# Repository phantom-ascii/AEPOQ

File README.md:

# AEPOQ
## born to be different

AEPOQ was created by a 14 year old kid. I created AEPOQ to study on keyboard layouts and matricies. "Why" you may ask... Well i want to creat a laptop in the next 2 years and what better way to learn about hardware and laptops than making a keyboard (there are proably alot of better ways.) Unfortunately i could not add my full master step die to githubs large file limit and i didnt have time to set up lfs or smth like that cause im leaving for school in 2 hours. Anyways the keyboard is a 68 key 65% keyboard designed for productivity. It has a rotaty switch and an oled to make it special. AND A CANDY HOLDER ON THE RIGHT.Heres some eye candy:

 I used a normal mattix for yhe key switches and a raspberry pi pico for the mcu. the firmware is a test and im not expecting it to work. i will fix it once i actually build the keyboard as that is what i usually do. The keyboard case is at a 6.3~ slant for imprived erganomics. Everything was designed me using models as a guide from open source repositorys. This project is also published on the hackclub programn, forge. I will be using cherry mx keyswitches and generic key caps. The rotary endoer is a ec11 from alps. the oled is a generic 0.91 oled 4 pin header and the mcu is a raspberry pi pico. The keyswitch layout is a generic 65% stagered QWERTY for productivity and general erganomics. If you want to rip any models from this repo go ahead. Its open source anyways.

 Here is the BOM:
 # 65% Custom Keyboard - Master Bill of Materials

## 1. Electronics & Hardware (AliExpress)

| Component | Store | Spec / Description | Price (USD) | Order Link |
| :--- | :--- | :--- | :--- | :--- |
| **Microcontroller** | WeAct Studio Official Store | RP2040 (8MB Black Edition) | $5.16 | [RP2040 Pico Board](https://www.aliexpress.com/item/1005003708090298.html) |
| **Diodes** | Chinese Super Electronic market | 1N4148 SOD-123 SMD Diodes (1000-pack) | $4.54 | [1N4148 SOD-123 Diodes](https://www.aliexpress.com/item/32354597825.html) |
| **Rotary Encoder** | DQLZV Official Store | EC11 Encoder 20mm Half-Handle (5-pack) | $2.85 | [EC11 Rotary Encoder](https://www.aliexpress.com/w/wholesale-digital-encoder-ec11.html) |
| **OLED Display** | diymore Alice1101983 Store | 0.91" 128x32 I2C Display Module | $3.09 | [0.91" I2C OLED Module](https://www.aliexpress.com/item/32815893431.html) |
| **Switches** | The Powerpuff Girls Switch Store | Cherry Switches (70-pack) | $26.58 | [Cherry MX Switches](https://www.aliexpress.com/item/100504669940336.html) |
| **Stabilizers** | YMDK Store | Screw-In PCB Mount Stabilizer Set | $18.62 | [YMDK PCB Stabilizers](https://www.aliexpress.com/item/1005012115758953.html) |
| **Keycaps** | Melokey Store | Line Gradient Side-Shine Cherry PBT | $18.32 | [Side-Shine PBT Keycaps](https://www.aliexpress.com/w/wholesale-keycaps-65.html) |
| **Heat-Set Inserts** | Zenhosit Store | Brass Threaded Inserts M2/M2.5/M3 (220-pack) | $4.91 | [M2 Brass Inserts](https://www.aliexpress.com/item/1005010241559236.html) |
| **Choice Discount** | Choice Discounts | Applied Checkout Savings | -$7.07 | — |
| **AliExpress Shipping** | Choice / Standard | Expedited Combined Delivery | $0.00 | Free |
| **AliExpress Subtotal** | | | **$84.06** | |

---

## 2. PCB Fabrication & 3D Printing (JLCPCB / JLC3DP)

| Item | Service | Description | Price (USD) |
| :--- | :--- | :--- | :--- |
| **PCB Prototypes (`Aepoq_Y7`)** | JLCPCB | White Solder Mask, 1.6 mm, HASL (5-pack) | $22.60 |
| **Keyboard Case (`Case.step`)** | JLC3DP | 9600 Resin, White SLA 3D Print (1 pc) | $88.74 |
| **Keyboard Lid (`Lid.step`)** | JLC3DP | 9600 Resin, White SLA 3D Print (1 pc) | $13.04 |
| **JLCPCB Shipping** | Standard / Express | Package Weight: 3.01 kg | $90.06 |
| **JLCPCB Coupons** | Checkout Coupon | Applied Savings | -$25.00 |
| **JLCPCB Subtotal** | | | **$189.44** |

---

## 3. Total Project Cost

| Category | Amount (USD) |
| :--- | :--- |
| **AliExpress Subtotal** | $84.06 |
| **JLCPCB Subtotal** | $189.44 |
| **Grand Total** | **$273.50** |

the whole build comes out to around $273, with jlcpcb taking up $189 of that. the shipping and case prices ended up pretty high because i intentionally went with a filled interior instead of hollowing it out. i've always hated light, cheap-feeling keyboards, so i wanted this build to have some serious weight to it and feel super solid on the desk even if it meant paying extra for the resin.

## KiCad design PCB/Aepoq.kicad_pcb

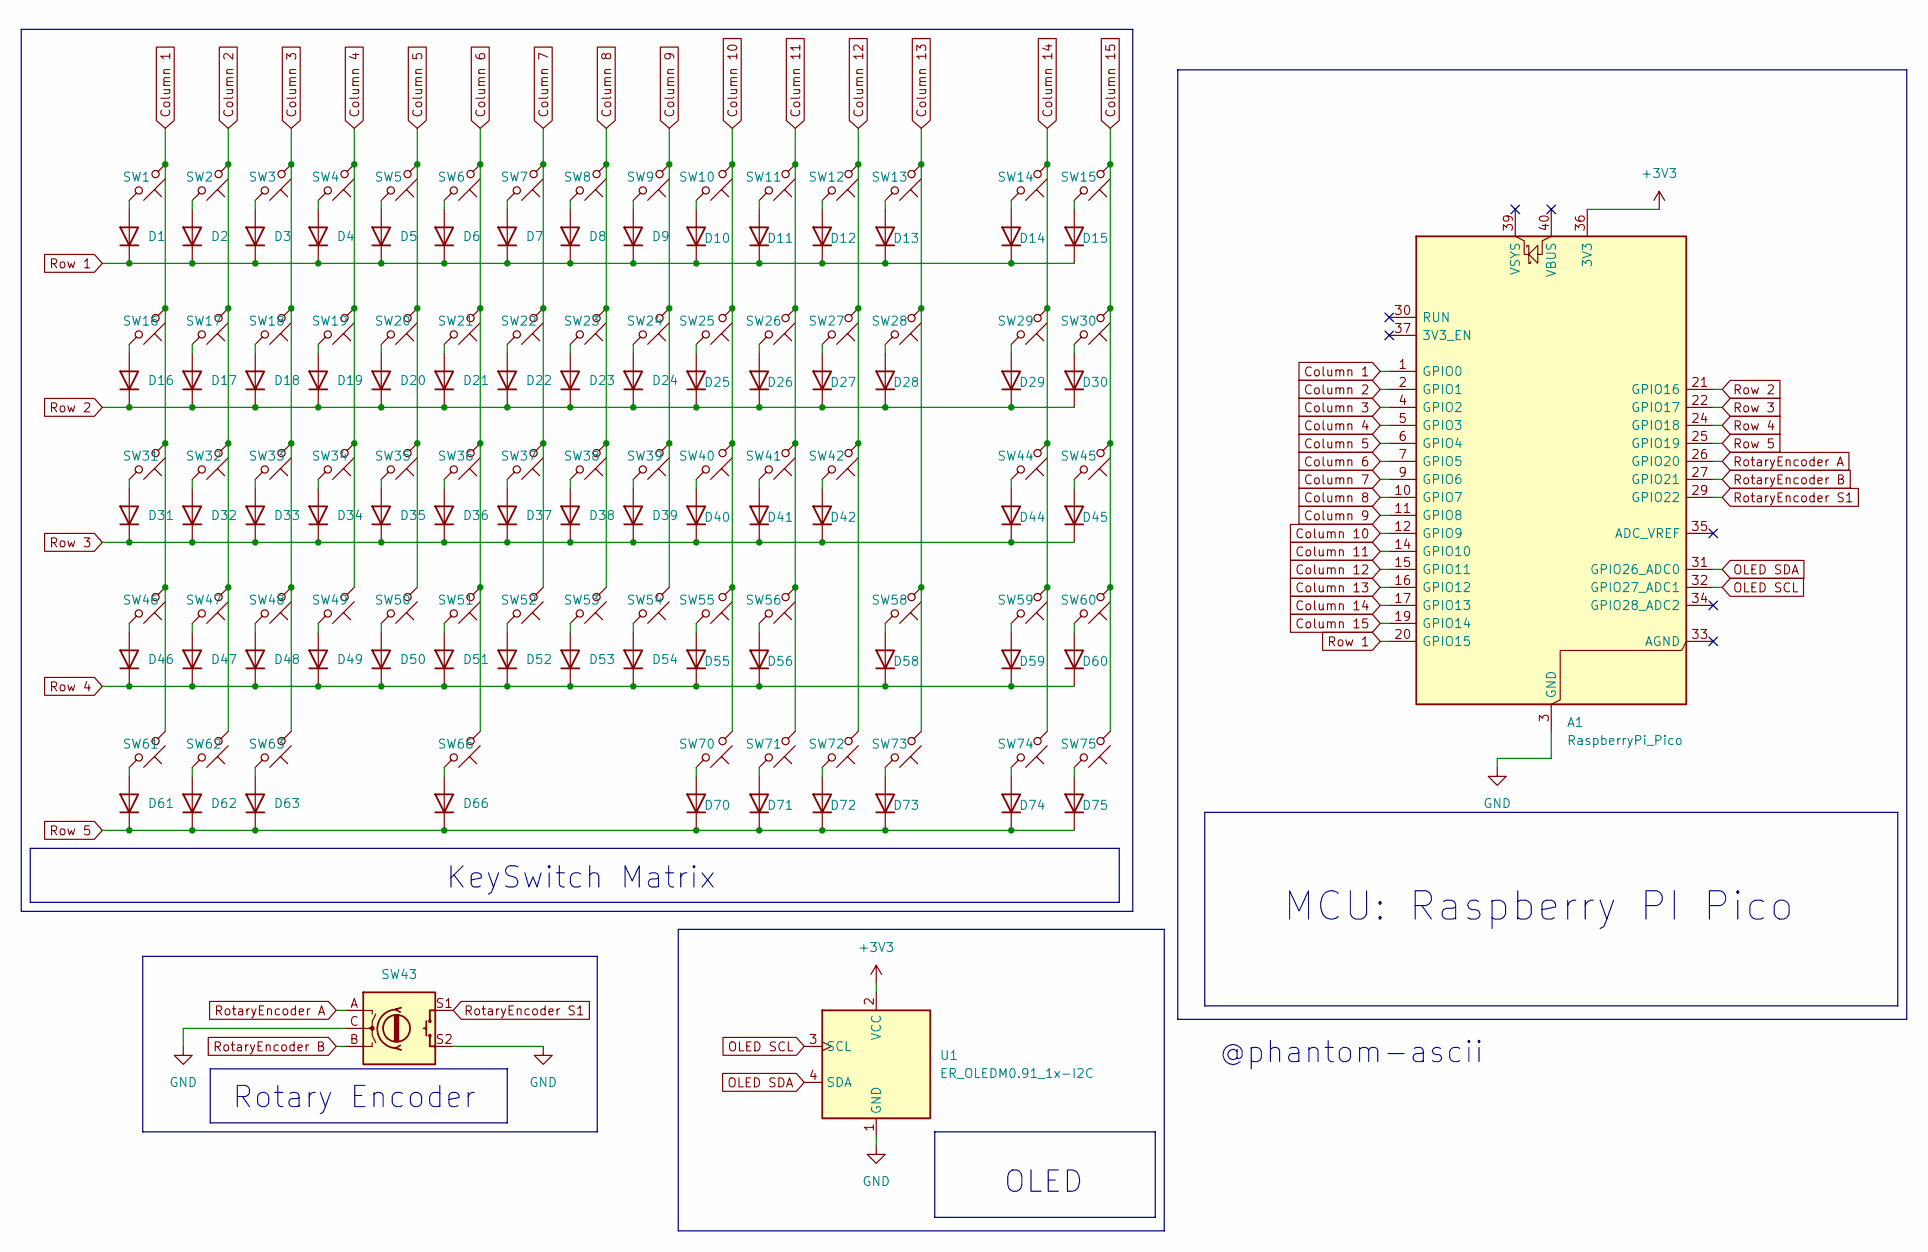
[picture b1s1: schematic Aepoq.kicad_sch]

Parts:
A1: RaspberryPi_Pico; Raspberry_Pi_Pico
D1, D2, D3, D4, D5, D6, D7, D8, D9, D10, D11, D12, D13, D14, D15, D16, D17, D18, D19, D20, D21, D22, D23, D24, D25, D26, D27, D28, D29, D30, D31, D32, D33, D34, D35, D36, D37, D38, D39, D40, D41, D42, D44, D45, D46, D47, D48, D49, D50, D51, D52, D53, D54, D55, D56, D58, D59, D60, D61, D62, D63, D66, D70, D71, D72, D73, D74, D75: 1N4148; D_DO-35_SOD27_P7.62mm_Horizontal
SW1, SW2, SW3, SW4, SW5, SW6, SW7, SW8, SW9, SW10, SW11, SW12, SW13, SW14, SW15, SW16, SW17, SW18, SW19, SW20, SW21, SW22, SW23, SW24, SW25, SW26, SW27, SW28, SW29, SW30, SW31, SW32, SW33, SW34, SW35, SW36, SW37, SW38, SW39, SW40, SW41, SW42, SW44, SW45, SW46, SW47, SW48, SW49, SW50, SW51, SW52, SW53, SW54, SW55, SW56, SW58, SW59, SW60, SW61, SW62, SW63, SW66, SW70, SW71, SW72, SW73, SW74, SW75: MX_SW_solder; SW_MX_1u
SW43: RotaryEncoder_Switch; RotaryEncoder_Alps_EC11E-Switch_Vertical_H20mm
U1: ER_OLEDM0.91_1x-I2C

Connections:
+3V3: A1.36 (3V3), U1.2 (VCC)
Column 1: A1.1 (GPIO0), SW1.1, SW16.1, SW31.1, SW46.1, SW61.1
Column 2: A1.2 (GPIO1), SW2.1, SW17.1, SW32.1, SW47.1, SW62.1
Column 3: A1.4 (GPIO2), SW3.1, SW18.1, SW33.1, SW48.1, SW63.1
Column 4: A1.5 (GPIO3), SW4.1, SW19.1, SW34.1, SW49.1
Column 5: A1.6 (GPIO4), SW5.1, SW20.1, SW35.1, SW50.1
Column 6: A1.7 (GPIO5), SW6.1, SW21.1, SW36.1, SW51.1, SW66.1
Column 7: A1.9 (GPIO6), SW7.1, SW22.1, SW37.1, SW52.1
Column 8: A1.10 (GPIO7), SW8.1, SW23.1, SW38.1, SW53.1
Column 9: A1.11 (GPIO8), SW9.1, SW24.1, SW39.1, SW54.1
Column 10: A1.12 (GPIO9), SW10.1, SW25.1, SW40.1, SW55.1, SW70.1
Column 11: A1.14 (GPIO10), SW11.1, SW26.1, SW41.1, SW56.1, SW71.1
Column 12: A1.15 (GPIO11), SW12.1, SW27.1, SW42.1, SW72.1
Column 13: A1.16 (GPIO12), SW13.1, SW28.1, SW58.1, SW73.1
Column 14: A1.17 (GPIO13), SW14.1, SW29.1, SW44.1, SW59.1, SW74.1
Column 15: A1.19 (GPIO14), SW15.1, SW30.1, SW45.1, SW60.1, SW75.1
GND: A1.3 (GND), A1.8 (GND), A1.13 (GND), A1.18 (GND), A1.23 (GND), A1.28 (GND), A1.38 (GND), SW43.C, SW43.S2, U1.1 (GND)
unnamed: D1.2 (A), SW1.2
unnamed: D2.2 (A), SW2.2
unnamed: D3.2 (A), SW3.2
unnamed: D4.2 (A), SW4.2
unnamed: D5.2 (A), SW5.2
unnamed: D6.2 (A), SW6.2
unnamed: D7.2 (A), SW7.2
unnamed: D8.2 (A), SW8.2
unnamed: D9.2 (A), SW9.2
unnamed: D10.2 (A), SW10.2
unnamed: D11.2 (A), SW11.2
unnamed: D12.2 (A), SW12.2
unnamed: D13.2 (A), SW13.2
unnamed: D14.2 (A), SW14.2
unnamed: D15.2 (A), SW15.2
unnamed: D16.2 (A), SW16.2
unnamed: D17.2 (A), SW17.2
unnamed: D18.2 (A), SW18.2
unnamed: D19.2 (A), SW19.2
unnamed: D20.2 (A), SW20.2
unnamed: D21.2 (A), SW21.2
unnamed: D22.2 (A), SW22.2
unnamed: D23.2 (A), SW23.2
unnamed: D24.2 (A), SW24.2
unnamed: D25.2 (A), SW25.2
unnamed: D26.2 (A), SW26.2
unnamed: D27.2 (A), SW27.2
unnamed: D28.2 (A), SW28.2
unnamed: D29.2 (A), SW29.2
unnamed: D30.2 (A), SW30.2
unnamed: D31.2 (A), SW31.2
unnamed: D32.2 (A), SW32.2
unnamed: D33.2 (A), SW33.2
unnamed: D34.2 (A), SW34.2
unnamed: D35.2 (A), SW35.2
unnamed: D36.2 (A), SW36.2
unnamed: D37.2 (A), SW37.2
unnamed: D38.2 (A), SW38.2
unnamed: D39.2 (A), SW39.2
unnamed: D40.2 (A), SW40.2
unnamed: D41.2 (A), SW41.2
unnamed: D42.2 (A), SW42.2
unnamed: D44.2 (A), SW44.2
unnamed: D45.2 (A), SW45.2
unnamed: D46.2 (A), SW46.2
unnamed: D47.2 (A), SW47.2
unnamed: D48.2 (A), SW48.2
unnamed: D49.2 (A), SW49.2
unnamed: D50.2 (A), SW50.2
unnamed: D51.2 (A), SW51.2
unnamed: D52.2 (A), SW52.2
unnamed: D53.2 (A), SW53.2
unnamed: D54.2 (A), SW54.2
unnamed: D55.2 (A), SW55.2
unnamed: D56.2 (A), SW56.2
unnamed: D58.2 (A), SW58.2
unnamed: D59.2 (A), SW59.2
unnamed: D60.2 (A), SW60.2
unnamed: D61.2 (A), SW61.2
unnamed: D62.2 (A), SW62.2
unnamed: D63.2 (A), SW63.2
unnamed: D66.2 (A), SW66.2
unnamed: D70.2 (A), SW70.2
unnamed: D71.2 (A), SW71.2
unnamed: D72.2 (A), SW72.2
unnamed: D73.2 (A), SW73.2
unnamed: D74.2 (A), SW74.2
unnamed: D75.2 (A), SW75.2
OLED SCL: A1.32 (GPIO27_ADC1), U1.3 (SCL)
OLED SDA: A1.31 (GPIO26_ADC0), U1.4 (SDA)
RotaryEncoder A: A1.26 (GPIO20), SW43.A
RotaryEncoder B: A1.27 (GPIO21), SW43.B
RotaryEncoder S1: A1.29 (GPIO22), SW43.S1
Row 1: A1.20 (GPIO15), D1.1 (K), D2.1 (K), D3.1 (K), D4.1 (K), D5.1 (K), D6.1 (K), D7.1 (K), D8.1 (K), D9.1 (K), D10.1 (K), D11.1 (K), D12.1 (K), D13.1 (K), D14.1 (K), D15.1 (K)
Row 2: A1.21 (GPIO16), D16.1 (K), D17.1 (K), D18.1 (K), D19.1 (K), D20.1 (K), D21.1 (K), D22.1 (K), D23.1 (K), D24.1 (K), D25.1 (K), D26.1 (K), D27.1 (K), D28.1 (K), D29.1 (K), D30.1 (K)
Row 3: A1.22 (GPIO17), D31.1 (K), D32.1 (K), D33.1 (K), D34.1 (K), D35.1 (K), D36.1 (K), D37.1 (K), D38.1 (K), D39.1 (K), D40.1 (K), D41.1 (K), D42.1 (K), D44.1 (K), D45.1 (K)
Row 4: A1.24 (GPIO18), D46.1 (K), D47.1 (K), D48.1 (K), D49.1 (K), D50.1 (K), D51.1 (K), D52.1 (K), D53.1 (K), D54.1 (K), D55.1 (K), D56.1 (K), D58.1 (K), D59.1 (K), D60.1 (K)
Row 5: A1.25 (GPIO19), D61.1 (K), D62.1 (K), D63.1 (K), D66.1 (K), D70.1 (K), D71.1 (K), D72.1 (K), D73.1 (K), D74.1 (K), D75.1 (K)

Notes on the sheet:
Rotary Encoder
OLED
MCU: Raspberry PI Pico
@phantom-ascii
KeySwitch Matrix

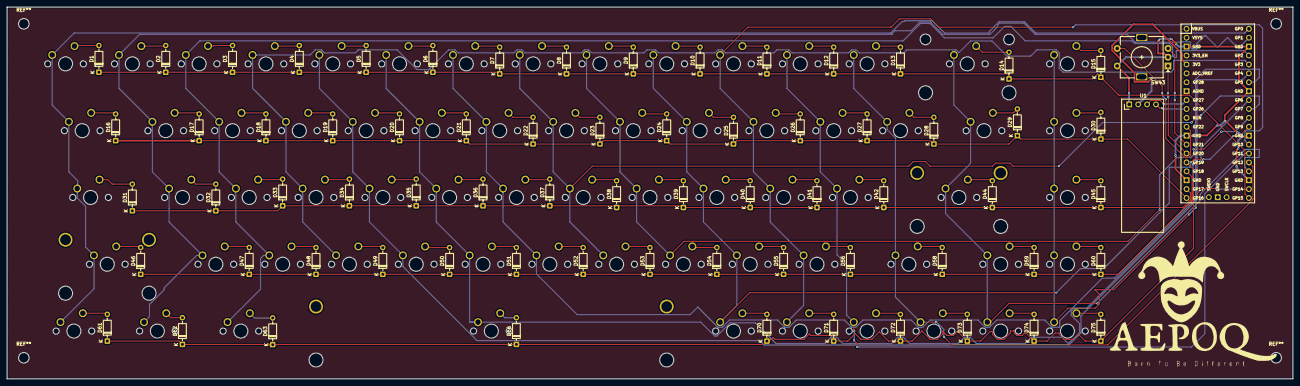
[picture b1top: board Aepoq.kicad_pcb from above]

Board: 2 copper layers, 366.7 x 106.0 mm, 139 parts (1 on the bottom side), 95 nets.

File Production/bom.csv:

Designator,Footprint,Quantity,Value,LCSC Part #
A1,Raspberry_Pi_Pico,1,RaspberryPi_Pico,
"D1, D10, D11, D12, D13, D14, D15, D16, D17, D18, D19, D2, D20, D21, D22, D23, D24, D25, D26, D27, D28, D29, D3, D30, D31, D32, D33, D34, D35, D36, D37, D38, D39, D4, D40, D41, D42, D44, D45, D46, D47, D48, D49, D5, D50, D51, D52, D53, D54, D55, D56, D58, D59, D6, D60, D61, D62, D63, D66, D7, D70, D71, D72, D73, D74, D75, D8, D9",D_DO-35_SOD27_P7.62mm_Horizontal,68,1N4148,
"SW1, SW10, SW11, SW12, SW13, SW14, SW15, SW16, SW17, SW18, SW19, SW2, SW20, SW21, SW22, SW23, SW24, SW25, SW26, SW27, SW28, SW29, SW3, SW30, SW31, SW32, SW33, SW34, SW35, SW36, SW37, SW38, SW39, SW4, SW40, SW41, SW42, SW44, SW45, SW46, SW47, SW48, SW49, SW5, SW50, SW51, SW52, SW53, SW54, SW55, SW56, SW58, SW59, SW6, SW60, SW61, SW62, SW63, SW66, SW7, SW70, SW71, SW72, SW73, SW74, SW75, SW8, SW9",SW_MX_1u,68,MX_SW_solder,
SW43,RotaryEncoder_Alps_EC11E-Switch_Vertical_H20mm,1,RotaryEncoder_Switch,
U1,ER_OLEDM0.91_1x-I2C,1,ER_OLEDM0.91_1x-I2C,
